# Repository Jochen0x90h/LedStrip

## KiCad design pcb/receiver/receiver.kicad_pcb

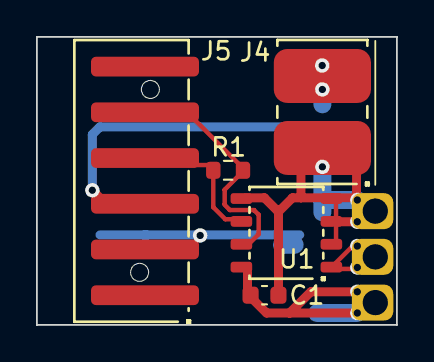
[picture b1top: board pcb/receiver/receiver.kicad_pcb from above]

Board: 2 copper layers, 20.0 x 16.0 mm, 7 parts (1 on the bottom side), 6 nets.

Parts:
C1: 100n; C_0603_1608Metric
J1: Conn_01x02_Socket; WAGO2061-602
J3: Conn_01x05_Socket; HolesL
J4: Conn_01x02; Kyocera-009176002001906
J5: Conn_01x04; Harting14110413002000
R1: 120R; R_0603_1608Metric
U1: SP485CN; SP485

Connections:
+5V: C1.1, J3.3, U1.8 (VCC)
+15V: J1.2, J4.2, J5.2
DATA: J3.2, U1.1 (RO)
GND: C1.2, J1.1, J3.1, J4.1, J5.1, U1.2 (~RE), U1.3 (DE), U1.4 (DI), U1.5 (GND)
RS485_A: J5.3, R1.1, U1.6 (A)
RS485_B: J5.4, R1.2, U1.7 (B)

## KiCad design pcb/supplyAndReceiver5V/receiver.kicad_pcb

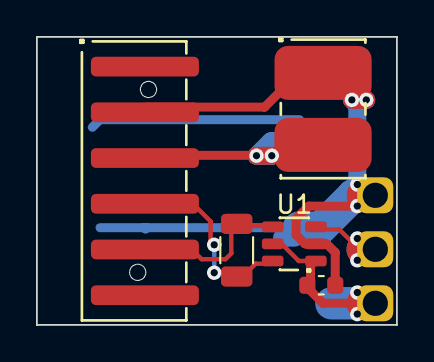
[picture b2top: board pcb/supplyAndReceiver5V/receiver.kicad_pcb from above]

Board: 2 copper layers, 20.0 x 16.0 mm, 7 parts (1 on the bottom side), 6 nets.

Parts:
C1: 100n; C_0603_1608Metric
J1: WAGO 2061-602; WAGO2061-602
J2: har-flexicon 2,54 MSH-4; Harting14110413002000
J3: Conn_01x05_Socket; SolderHoles3pin10mm
J4: Kyocera-009176002001906
R1: 120R; R_1206_3216Metric
U1: ISL3281E

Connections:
+5V: C1.1, J3.3, U1.1 (VCC), U1.5 (RE)
+15V: J1.2, J2.2, J4.2
DATA: J3.2, U1.3 (RO)
GND: C1.2, J1.1, J2.1, J3.1, J4.1, U1.2 (GND)
RS485_A: J2.3, R1.1, U1.6 (A)
RS485_B: J2.4, R1.2, U1.4 (B)
